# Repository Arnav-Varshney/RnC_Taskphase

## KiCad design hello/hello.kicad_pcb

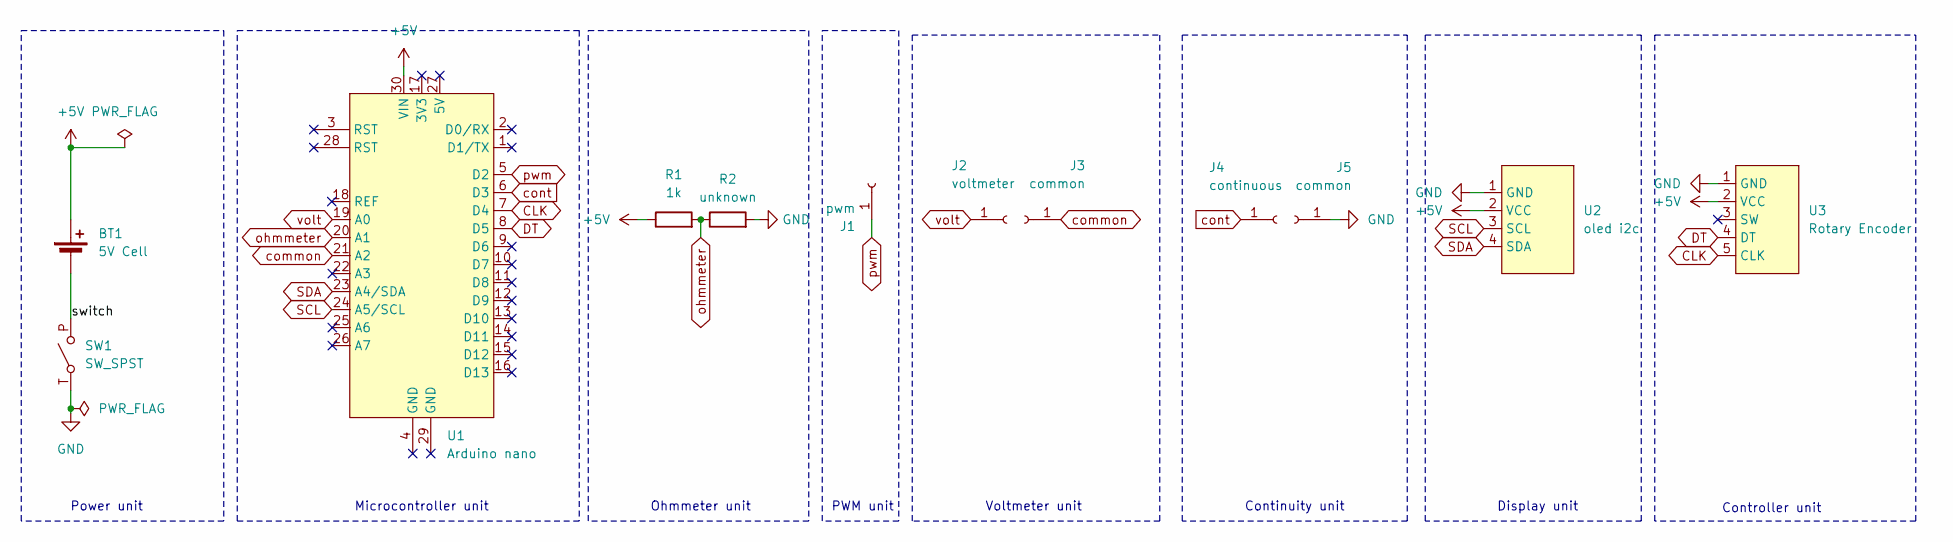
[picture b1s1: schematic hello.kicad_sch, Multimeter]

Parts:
BT1: 5V Cell; BatteryHolder_Keystone_2479_3xAAA
J1: pwm; PinSocket_1x01_P1.27mm_Vertical
J2: voltmeter; PinSocket_1x01_P1.27mm_Vertical
J3, J5: common; PinSocket_1x01_P1.27mm_Vertical
J4: continuous; PinSocket_1x01_P1.27mm_Vertical
R1: 1k; R_Axial_DIN0204_L3.6mm_D1.6mm_P1.90mm_Vertical
R2: unknown; PinSocket_1x02_P1.27mm_Vertical
SW1: SW_SPST; JUDCOSPST
U1: Arduino nano; Arduino_nano
U2: oled i2c; PinSocket_1x04_P1.27mm_Vertical
U3: Rotary Encoder; PinSocket_1x05_P1.27mm_Vertical

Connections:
+5V: BT1.1 (+), R1.1, U1.30 (VIN), U2.2 (VCC), U3.2 (VCC)
/switch: BT1.2 (-), SW1.P (B)
CLK: U1.7 (D4), U3.5 (CLK)
DT: U1.8 (D5), U3.4 (DT)
GND: J5.1, R2.2, SW1.T (A), U2.1 (GND), U3.1 (GND)
SCL: U1.24 (A5/SCL), U2.3 (SCL)
SDA: U1.23 (A4/SDA), U2.4 (SDA)
common: J3.1, U1.21 (A2)
cont: J4.1, U1.6 (D3)
ohmmeter: R1.2, R2.1, U1.20 (A1)
pwm: J1.1, U1.5 (D2)
volt: J2.1, U1.19 (A0)

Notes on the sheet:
PWM unit
Ohmmeter unit
Microcontroller unit
Controller unit
Continuity unit
Voltmeter unit
Display unit
Power unit

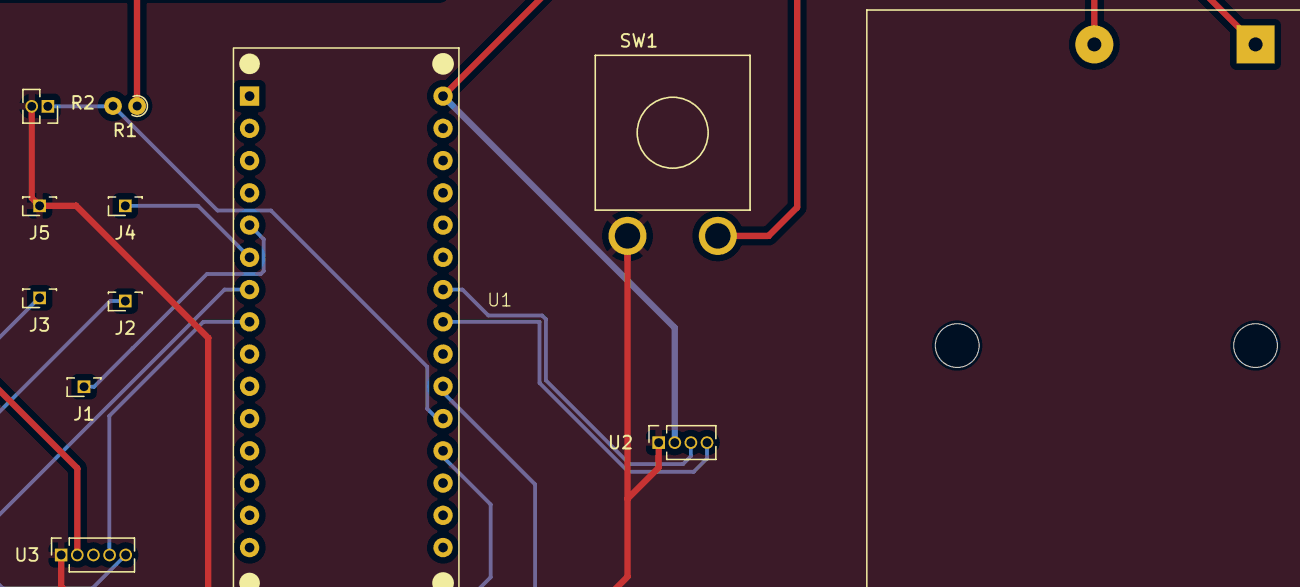
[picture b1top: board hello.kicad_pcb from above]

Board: 2 copper layers, 12 parts (0 on the bottom side), 12 nets.

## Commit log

2024-12-12 deleting test files
2024-12-13 updated kicad
2024-12-16 mini project
2024-12-16 revision
2024-12-21 final pcb
2024-12-21 updates to final pcb design
2024-12-24 revision to pcb layout
